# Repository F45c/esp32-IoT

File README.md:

# Esp32-IoT-Sensors

An Esp32 packed with sensors for IoT use. It uses the Esp32-C3-Mini-1 module that includes an antenna and it receives data from lots of sensors like heart rate, temperature, flame detector and much more.

#### These are the Sensors:

> DHT11
> - Temperature & Humidity
> 
> BMP280
> - Barometer & Air Pressure
> 
> AHT20
> - Temperature & Air Humidity
> 
> MQ-135
> - Air Quality & Gas detection
> 
> MPU-6050
> - Accelerometer & Gyro
> 
> HC-SR501
> - Motion Sensor
> 
> DS18B20
> - Temperature
> 
> MAX30102
> - Heart Rate & Oxigen Saturation
> 
> IR Flame Detector
> 
> Light Dependent Resistor

### Finished Build
I finished the PCB assembly. Since I'm a beginner, I was struggling a lot with the tiny solder joints. The most annoying parts to solder were definitely the BMP280 and the USB-C connector because the pins are so tiny and are easily bridged. Soldering the LEDs failed a few times because I would test them before for polarity check and while picking the up with the tweezers, they would move and I accidentally soldered them wrong a few times.

Originally, I would have unsoldered the MQ-135 gas sensor and solder it to my pcb, but I wasn't able to because of how to module is designed so I stuck the pins that are sticking out of the bottom of the board into my pcb and it fits.

I spaced everything tightly in the design and now that I built it, I find it hard to fully reach the Heart Rate sensor (2nd image bottom right), but since the Motion sensor is unpluggable, you can still use it.

## Why am I making this?

I'm building this sensor board for a presentation of mine about Internet of Things.
This will help me demonstrate the practical application of Esp32 Chips, low energy sensors and Telemetry using different Protocols like MQTT. The many different sensors will come in handy when the crowd can try their newly learned skills on programming this device. That's why I designed it very openly and you can clearly see how all the components are connected (when you unplug the motion sensor from the pin sockets)

## Design

I carefully checked that every sensor is in the right place and its functionality won't be blocked by other components (e.g. LDR, IR LED, ...). If you don't like the huge motion detector in the center, you can just unplug it because it's connected via Pin Sockets.

There are two trimmer for controlling the sensitivity of the gas sensor and flame detector respectively.

### PCB

The important points to mention in the PCB Design are the two Ground Planes which fill up all unused space on the front and back layers. Though, the space below the esp32's pcb antenna needs to be copper-free allowing the antenna to work without being blocked / the signal reflected.

### Schematic

### BOM
|Name|Purpose|Quantity|Total Cost (USD)|Link|Distributor|
|----|------|---|------|------------|-----------|
|PCB|PCB board|1|5.5||JLCPCB|
|HC-SR501|Motion sensor|1|4.05|https://www.amazon.com/-/de/dp/B09LVJ4DZX|Amazon|
|MQ-135|Gas Sensor|1|4.99|https://www.amazon.com/dp/B0GSRWSLB1|Amazon|
|PCBA|PCB Assembly Parts|1|25.60||JLCPCB|

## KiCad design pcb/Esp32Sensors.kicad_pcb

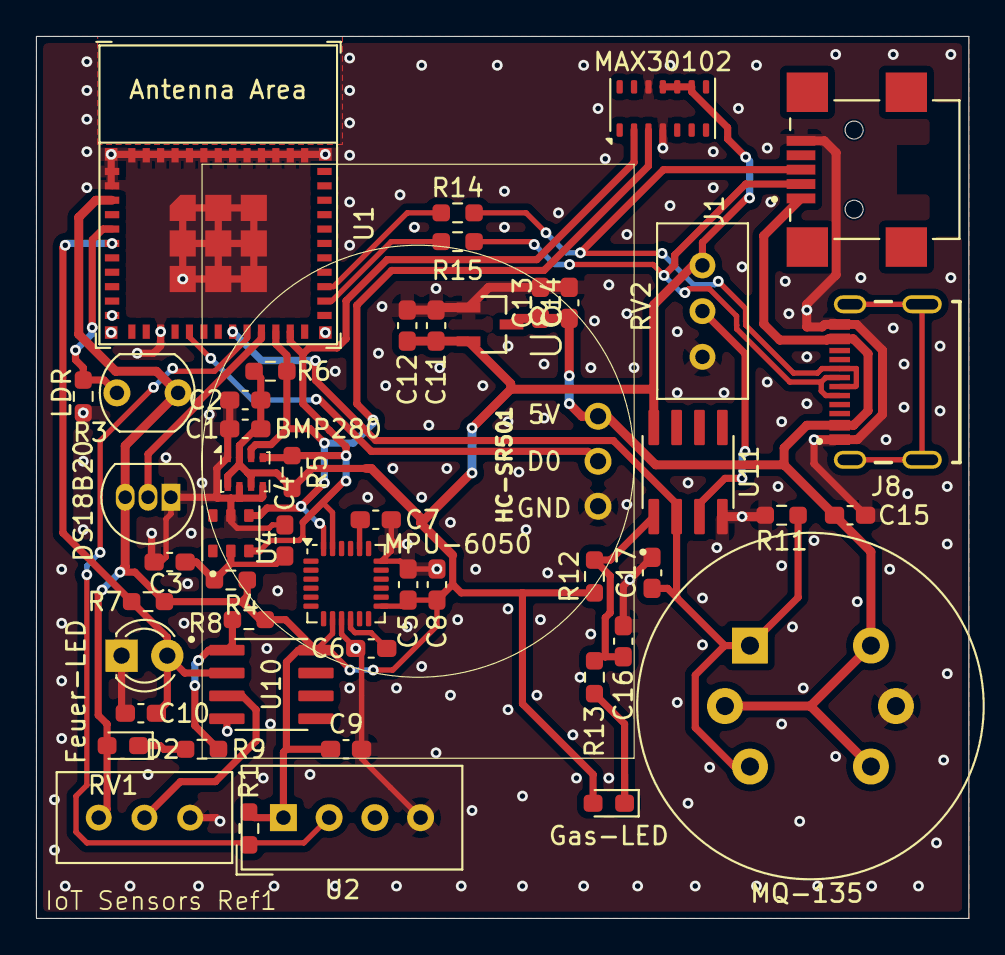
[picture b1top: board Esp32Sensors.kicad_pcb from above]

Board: 2 copper layers, 51.8 x 49.0 mm, 50 parts (0 on the bottom side), 26 nets.

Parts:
C1, C2, C4, C5, C6, C9, C10, C12, C14, C15, C16, C17: 100nF; C_0603_1608Metric_Pad1.08x0.95mm_HandSolder
C3: 10uF; C_0603_1608Metric_Pad1.08x0.95mm_HandSolder
C7: 2.2nF; C_0603_1608Metric_Pad1.08x0.95mm_HandSolder
C8: 10nF; C_0603_1608Metric_Pad1.08x0.95mm_HandSolder
C11, C13: 1uF; C_0603_1608Metric_Pad1.08x0.95mm_HandSolder
D2: LED; LED_0603_1608Metric_Pad1.05x0.95mm_HandSolder
DS18B20: DS18B20; TO-92_Inline
Feuer-LED: IR Sensor; LED_D3.0mm
Gas-LED: LED; LED_0603_1608Metric_Pad1.05x0.95mm_HandSolder
HC-SR501: Motion Sensor; HC-SR501
J1: GMSB0532112YEU; AMPHENOL_GMSB0532112YEU
J8: USB4215-03-A_REVA; GCT_USB4215-03-A_REVA
LDR: LDR07; R_LDR_5.1x4.3mm_P3.4mm_Vertical
MAX30102: MAX30102; Maxim_OLGA-14_3.3x5.6mm_P0.8mm
MPU-6050: MPU-6050; InvenSense_QFN-24_4x4mm_P0.5mm
MQ-135: MQ-6
R1: 5kohm; R_0603_1608Metric_Pad0.98x0.95mm_HandSolder
R3, R7, R8, R12: 10kohm; R_0603_1608Metric_Pad0.98x0.95mm_HandSolder
R4: 330ohm; R_0603_1608Metric_Pad0.98x0.95mm_HandSolder
R5, R6: 2k-4.7k; R_0603_1608Metric_Pad0.98x0.95mm_HandSolder
R9, R13: 100ohm; R_0603_1608Metric_Pad0.98x0.95mm_HandSolder
R11: 33k; R_0603_1608Metric_Pad0.98x0.95mm_HandSolder
R14, R15: 22ohm; R_0603_1608Metric_Pad0.98x0.95mm_HandSolder
RV1, RV2: 10k poty; Potentiometer_Bourns_3296W_Vertical
U1: ESP32-C3-MINI-1
U2: DHT11; Aosong_DHT11_5.5x12.0_P2.54mm
U4: AHT20; PSON100P300X300X110-6N
U5: BMP280; Bosch_LGA-8_2x2.5mm_P0.65mm_ClockwisePinNumbering
U8: MCP1702T-3302E_CB; SOT95P255X145-3N
U10, U11: LM393; SOIC127P600X265-8N

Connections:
+3.3V: C1.2, C2.2, C5.1, C8.1, C9.2, C11.2, C12.2, D2.2 (A), DS18B20.3 (V_{DD}), Gas-LED.2 (A), LDR.2, MAX30102.9 (VLED+), MAX30102.10 (VLED+), MAX30102.11 (VDD), MPU-6050.8 (VLOGIC), MPU-6050.13 (VDD), R1.2, R4.1, R5.1, R6.1, R7.2, R8.2, R12.2, RV1.1, RV2.1, U1.3 (3V3), U2.1 (VDD), U5.2 (CSB), U5.6 (VDDIO), U5.8 (VDD), U8.2 (VOUT), U10.8 (V+), U11.8 (V+)
+5V: C13.2, C14.2, C15.1, HC-SR501.3, J1.1 (VBUS), J8.A4_B9 (VBUS_A), J8.B4_A9 (VBUS_B), MQ-135.2 (VH+), MQ-135.4 (A2), MQ-135.6 (A1), U8.3 (VIN)
GND: C1.1, C2.1, C3.2, C4.2, C5.2, C6.2, C7.2, C8.2, C9.1, C10.1, C11.1, C12.1, C13.1, C14.1, C15.2, C16.2, C17.2, DS18B20.1 (GND), Feuer-LED.1 (K), HC-SR501.1, J1.5 (GND), J8.A1_B12 (GND_A), J8.B1_A12 (GND_B), MAX30102.4 (PGND), MAX30102.12 (GND), MPU-6050.9 (AD0), MPU-6050.18 (GND), MQ-135.5 (VH-), R3.1, R11.2, RV1.3, RV2.3, U1.1 (GND), U1.2 (GND), U1.11 (GND), U1.14 (GND), U1.36 (GND), U1.37 (GND), U1.38 (GND), U1.39 (GND), U1.40 (GND), U1.41 (GND), U1.42 (GND), U1.43 (GND), U1.44 (GND), U1.45 (GND), U1.46 (GND), U1.47 (GND), U1.48 (GND), U1.49 (GND), U1.50 (GND), U1.51 (GND), U1.52 (GND), U1.53 (GND), U2.4 (GND), U4.5 (GND), U5.1 (GND), U5.5 (SDO), U5.7 (GND), U8.1 (GND), U10.4 (V-), U11.4 (V-)
unnamed: C16.1, R12.1, R13.1, U11.1
unnamed: C10.2, Feuer-LED.2 (A), R7.1, U1.6 (GPIO3/ADC1_CH3), U10.2 (-)
unnamed: D2.1 (K), R9.2
unnamed: Gas-LED.1 (K), R13.2
unnamed: HC-SR501.2, U1.16 (GPIO10)
unnamed: J1.3 (D+), J8.A6 (DP1), J8.B6 (DP2), R14.1
unnamed: J1.2 (D-), J8.A7 (DN1), J8.B7 (DN2), R15.1
unnamed: J1.S1 (SHIELD), J1.S2 (SHIELD), J1.S3 (SHIELD), J1.S4 (SHIELD)
unnamed: J8.SH1 (SHIELD), J8.SH2 (SHIELD), J8.SH3 (SHIELD), J8.SH4 (SHIELD)
unnamed: R8.1, R9.1, U10.1
unnamed: LDR.1, R3.2, U1.5 (GPIO2/ADC1_CH2)
unnamed: C17.1, MQ-135.1 (B1), MQ-135.3 (B2), R11.1, U1.19 (GPIO5/ADC2_CH0), U11.2 (-)
unnamed: R1.1, U1.20 (GPIO6), U2.2 (DATA)
unnamed: DS18B20.2 (DQ), U1.21 (GPIO7)
unnamed: MAX30102.3 (SDA), MPU-6050.24 (SDA), R6.2, U1.22 (GPIO8), U4.4 (SDA), U5.3 (SDI)
unnamed: MAX30102.2 (SCL), MPU-6050.23 (SCL), R5.2, U1.23 (GPIO9), U4.3 (SCL), U5.4 (SCK)
unnamed: R15.2, U1.26 (GPIO18/USB_D-)
unnamed: R14.2, U1.27 (GPIO19/USB_D+)
unnamed: C3.1, C4.1, R4.2, U4.2 (VDD)
unnamed: C7.1, MPU-6050.20 (CPOUT)
unnamed: C6.1, MPU-6050.10 (REGOUT)
unnamed: RV1.2, U10.3 (+)
unnamed: RV2.2, U11.3 (+)

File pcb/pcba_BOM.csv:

"Reference","Qty","Value","DNP","Exclude from BOM","Exclude from Board","Footprint","Datasheet"
"C1,C2,C4,C5,C6,C9,C10,C12,C14,C15,C16,C17","12","100nF","","","","Capacitor_SMD:C_0603_1608Metric_Pad1.08x0.95mm_HandSolder",""
"C3","1","10uF","","","","Capacitor_SMD:C_0603_1608Metric_Pad1.08x0.95mm_HandSolder",""
"C7","1","2.2nF","","","","Capacitor_SMD:C_0603_1608Metric_Pad1.08x0.95mm_HandSolder",""
"C8","1","10nF","","","","Capacitor_SMD:C_0603_1608Metric_Pad1.08x0.95mm_HandSolder",""
"C11,C13","2","1uF","","","","Capacitor_SMD:C_0603_1608Metric_Pad1.08x0.95mm_HandSolder",""
"D1","1","IR Sensor","","","","LED_THT:LED_D3.0mm",""
"D2,D3","2","LED","","","","LED_SMD:LED_0603_1608Metric_Pad1.05x0.95mm_HandSolder",""
"HC-SR501","1","Motion Sensor","","","","HC-SR501-master:HC-SR501",""
"J1","1","GMSB0532112YEU","","","","GMSB0532112YEU:AMPHENOL_GMSB0532112YEU",""
"J8","1","USB4215-03-A_REVA","","","","USB4215-03-A_REVA:GCT_USB4215-03-A_REVA",""
"R1","1","5kohm","","","","Resistor_SMD:R_0603_1608Metric_Pad0.98x0.95mm_HandSolder",""
"R2","1","LDR07","","","","OptoDevice:R_LDR_5.1x4.3mm_P3.4mm_Vertical","http://www.tme.eu/de/Document/f2e3ad76a925811312d226c31da4cd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"
"R3,R7,R8,R10,R12","5","10kohm","","","","Resistor_SMD:R_0603_1608Metric_Pad0.98x0.95mm_HandSolder",""
"R4","1","330ohm","","","","Resistor_SMD:R_0603_1608Metric_Pad0.98x0.95mm_HandSolder",""
"R5,R6","2","2k-4.7k","","","","Resistor_SMD:R_0603_1608Metric_Pad0.98x0.95mm_HandSolder",""
"R9,R13","2","100ohm","","","","Resistor_SMD:R_0603_1608Metric_Pad0.98x0.95mm_HandSolder",""
"R11","1","33k","","","","Resistor_SMD:R_0603_1608Metric_Pad0.98x0.95mm_HandSolder",""
"R14,R15","2","22ohm","","","","Resistor_SMD:R_0603_1608Metric_Pad0.98x0.95mm_HandSolder",""
"RV1,RV2","2","10k poty","","","","Potentiometer_THT:Potentiometer_Bourns_3296W_Vertical",""
"U1","1","ESP32-C3-MINI-1","","","","PCM_Espressif:ESP32-C3-MINI-1","https://www.espressif.com/sites/default/files/documentation/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"
"U2","1","DHT11","","","","Sensor:Aosong_DHT11_5.5x12.0_P2.54mm","http://akizukidenshi.com/download/ds/aosong/DHT11.pdf"
"U3","1","DS18B20","","","","Package_TO_SOT_THT:TO-92_Inline","http://datasheets.maximintegrated.com/en/ds/DS18B20.pdf"
"U4","1","AHT20","","","","AHT20:PSON100P300X300X110-6N",""
"U5","1","BMP280","","","","Package_LGA:Bosch_LGA-8_2x2.5mm_P0.65mm_ClockwisePinNumbering","https://ae-bst.resource.bosch.com/media/_tech/media/datashee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"
"U6","1","MPU-6050","","","","Sensor_Motion:InvenSense_QFN-24_4x4mm_P0.5mm","https://invensense.tdk.com/wp-content/uploads/2015/02/MPU-60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"
"U7","1","MAX30102","","","","OptoDevice:Maxim_OLGA-14_3.3x5.6mm_P0.8mm","https://datasheets.maximintegrated.com/en/ds/MAX30102.pdf"
"U8","1","MCP1702T-3302E_CB","","","","MCP1702T-3302E_CB:SOT95P255X145-3N",""
"U9","1","MQ-6","","","","Sensor:MQ-6","https://www.winsen-sensor.com/d/files/semiconductor/mq-6.pdf"
"U10,U11","2","LM393","","","","LM393DR2G:SOIC127P600X265-8N","http://www.ti.com/lit/ds/symlink/lm393.pdf"
"U11","1","LM393","","","","LM393DR2G:SOIC127P600X265-8N","http://www.ti.com/lit/ds/symlink/lm393.pdf"

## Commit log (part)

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2026-06-08 added pcb files
2026-06-08 added 3d models
2026-06-08 added images
2026-06-08 new versions of images
2026-06-08 updated pcb files
2026-06-10 updated images
2026-06-10 updated schematic image
2026-06-10 Updated image links
2026-06-12 added bom.csv
2026-06-12 added bom to readme
